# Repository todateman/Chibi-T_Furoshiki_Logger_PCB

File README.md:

# Chibi-T Furoshiki Logger

M5Stack Basic / Core2 用の車両データロガー拡張基板（モジュール基板）です。

## 概要

本基板は M5Stack の M-BUS コネクタに接続するボトムモジュールとして動作し、以下のデータを収集・記録するためのロガー回路です。

- GNSS（GPS）モジュールからの位置情報（UART）
- 車両 ECU との UART 通信によるデータ
- BME280 センサーによる温湿度・気圧などの環境データ

## 特徴

- M5Stack M-BUS（2×15ピン）接続、Basic / Core2 の両方に対応した Module 基板
  - テンプレートは <https://github.com/botanicfields/KiCad6-Environment> の `M5Stack_module_fdm` を使用
- GNSS（GPS）モジュール接続用の UART 入力
- 車両 ECU との通信用 UART 入力
- Bosch BME280 搭載（I2C接続、アドレス `0x76`）による温湿度・気圧センシング
- MP1584EN-LF-Z による +12V → 5V / 3.3V 降圧レギュレータを内蔵
- ポリヒューズおよびショットキーダイオードによる電源保護

<!-- TODO: 基板写真・回路図スクリーンショットを追加 -->

## 主要部品

| Ref | 部品 | 役割 |
| --- | --- | --- |
| U1 | MP1584EN-LF-Z | 降圧DC-DCコンバータ（+12V → 5V/3.3V） |
| U2 | BME280 | 温湿度・気圧センサー（I2C） |
| J1 | M5Stack M-BUS | M5Stack Basic/Core2 との接続コネクタ |
| D1 | ショットキーダイオード | 電源保護 |
| F1 | ポリヒューズ | 電源保護 |

より詳細な部品表は、KiCad でプロジェクトを開き BOM を出力することで確認できます（後述）。

## リポジトリ構成

```txt
Chibi-T_Furoshiki_Logger.kicad_pro   KiCadプロジェクトファイル
Chibi-T_Furoshiki_Logger.kicad_sch   回路図
Chibi-T_Furoshiki_Logger.kicad_pcb   基板データ
C15051/                              MP1584EN-LF-Z用カスタムライブラリ（シンボル・フットプリント）
logos.pretty/                        シルク印刷用ロゴフットプリント
LICENSE.txt                          ライセンス
```

## 必要な環境

- KiCad 10.0 以降

## 使い方

1. `Chibi-T_Furoshiki_Logger.kicad_pro` を KiCad 10.0 以降で開きます。
2. 回路図・基板データを確認・編集できます。
3. ガーバーデータや部品表（BOM）、部品配置データ（CPL）の生成には、KiCad拡張「[Fabrication Toolkit](https://github.com/bennymeg/Fabrication-Toolkit)」を使用する想定で設定済みです（`fabrication-toolkit-options.json`）。  
   生成したデータは `production/` フォルダに出力されますが、このフォルダは `.gitignore` 対象のためリポジトリには含まれません。  
   各自の環境で生成してください。

## 免責事項

本プロジェクトは個人のホビープロジェクトです。車両への実装・使用は自己責任で行ってください。  
基板の動作および安全性について、いかなる保証も行いません。

## ライセンス

本プロジェクトは [MIT License](LICENSE.txt) の下で公開されています。

Copyright (c) 2026 Tomohiro Kusu

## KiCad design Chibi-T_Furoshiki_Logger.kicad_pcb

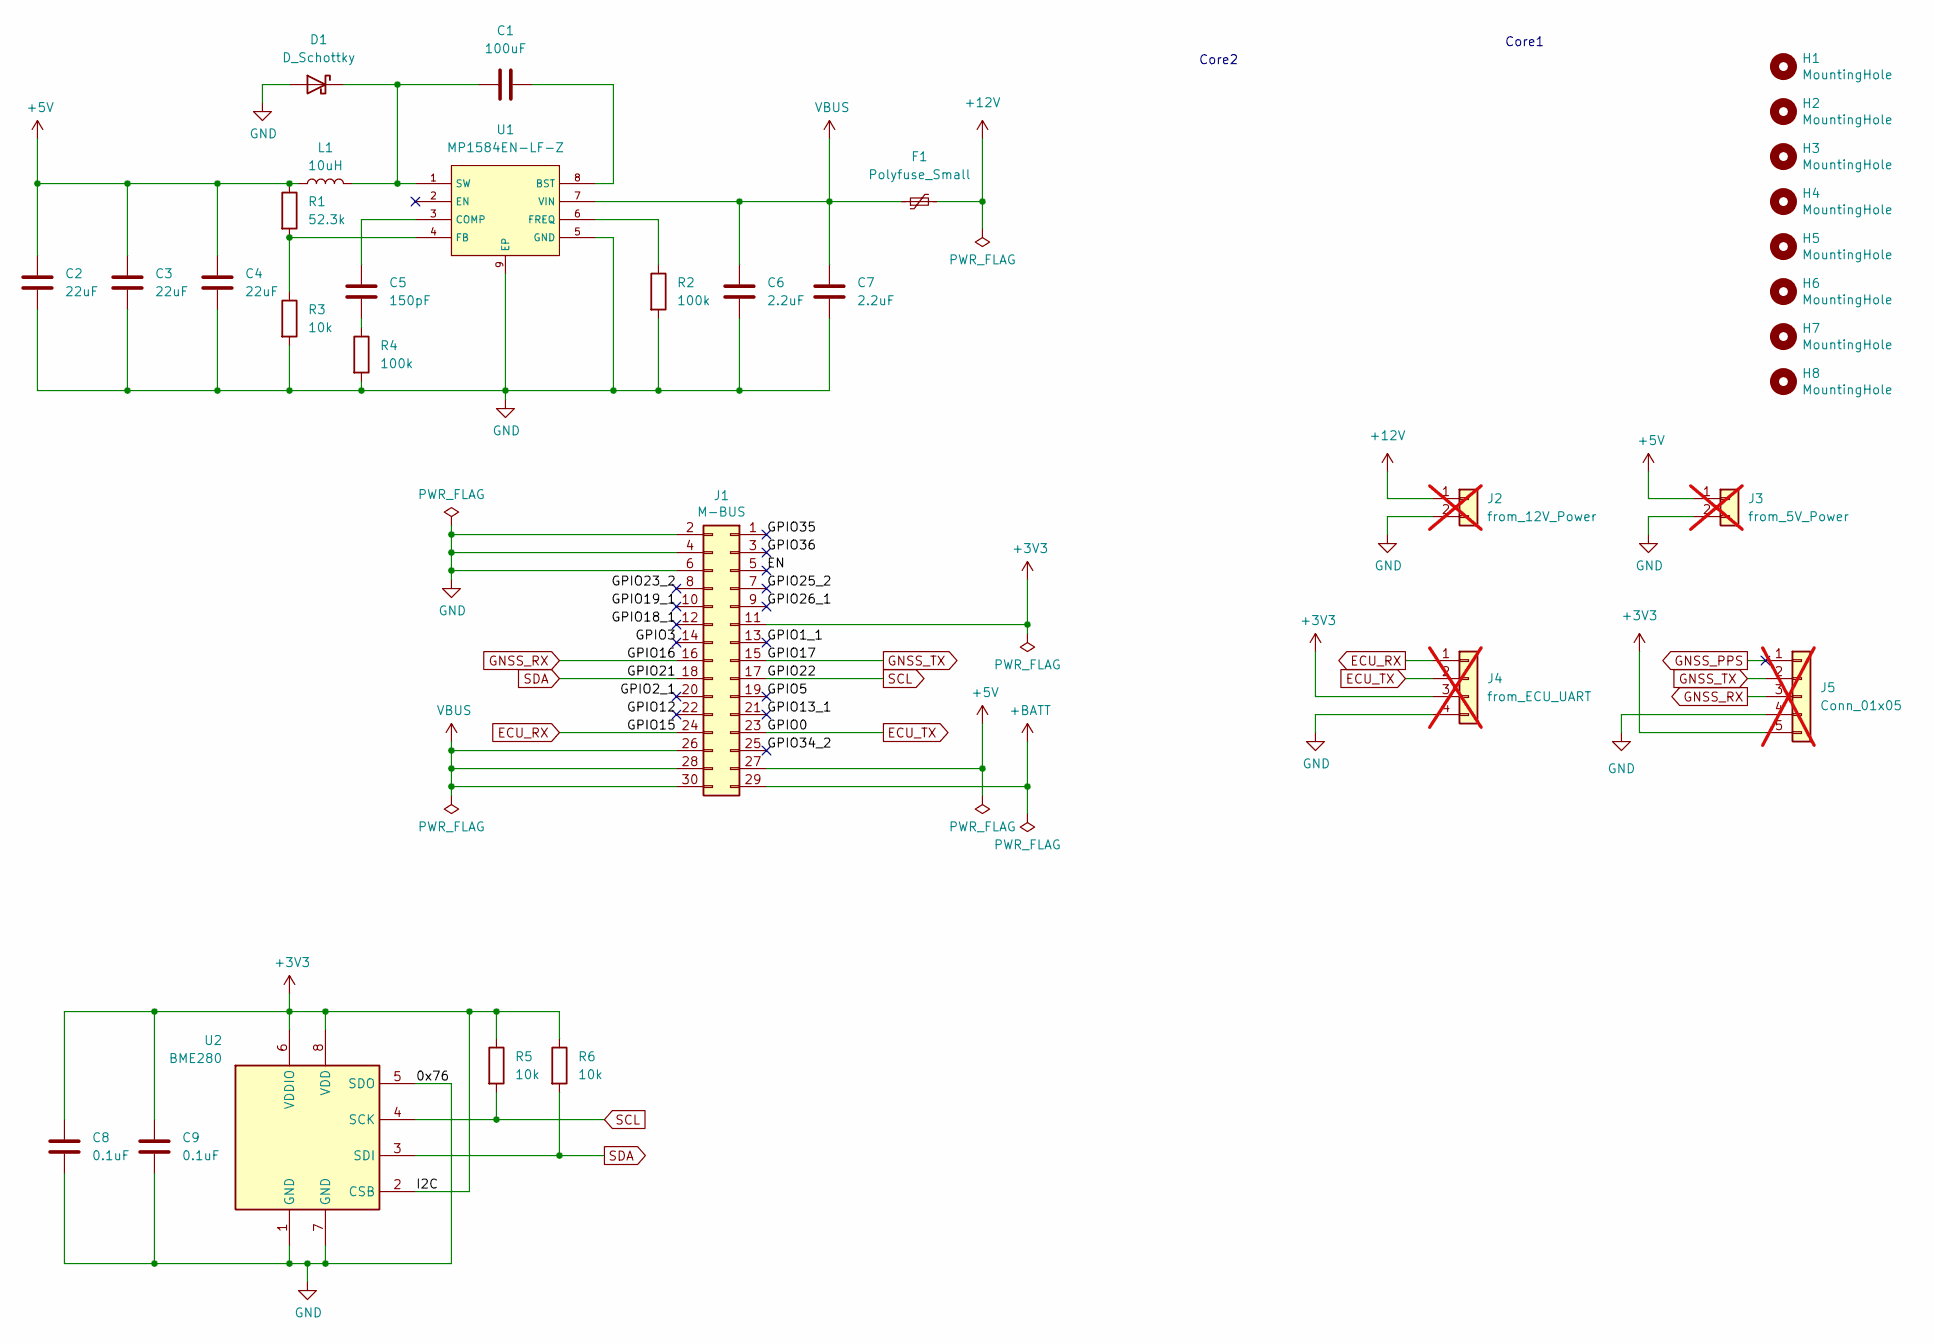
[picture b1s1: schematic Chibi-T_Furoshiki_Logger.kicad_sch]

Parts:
C1: 100uF; C_1206_3216Metric; LCSC C15008
C2, C3, C4: 22uF; C_0603_1608Metric; LCSC C59461
C5: 150pF; C_0603_1608Metric; LCSC C1594
C6, C7: 2.2uF; C_0805_2012Metric; LCSC C377773
C8, C9: 0.1uF; C_0402_1005Metric; LCSC C1525
D1: D_Schottky; D_SMA; LCSC C22452
F1: Polyfuse_Small; Fuse_1812_4532Metric; LCSC C28326708
H1, H2, H3, H4: MountingHole; BF@MountingHole_3.2mm_M3
H5, H6, H7, H8: MountingHole; BF@MountingHole_2.2mm_M2
J1: M-BUS; BF@M5Stack_MBUS
J2: from_12V_Power; PinSocket_1x02_P2.54mm_Vertical; not fitted
J3: from_5V_Power; PinSocket_1x02_P2.54mm_Vertical; not fitted
J4: from_ECU_UART; PinSocket_1x04_P2.54mm_Vertical; not fitted
J5: Conn_01x05; PinSocket_1x05_P2.54mm_Vertical; not fitted
L1: 10uH; L_Sunlord_SWPA3015S; LCSC C45403
R1: 52.3k; R_0603_1608Metric; LCSC C23198
R2, R4: 100k; R_0603_1608Metric; LCSC C25803
R3, R5, R6: 10k; R_0805_2012Metric; LCSC C17414
U1: MP1584EN-LF-Z; SOIC-8_L5.0-W4.0-P1.27-LS6.0-BL-EP2.0; Manufacturer Part MP1584EN-LF-Z; LCSC C15051
U2: BME280; Bosch_LGA-8_2.5x2.5mm_P0.65mm_ClockwisePinNumbering; LCSC C92489

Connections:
/EN: J1.5
/EN_1: J1.5
/EN_2: J1.5
/GPIO1_1: J1.13
/GPIO1_1_1: J1.13
/GPIO1_1_2: J1.13
/GPIO2_1: J1.20
/GPIO2_1_1: J1.20
/GPIO2_1_2: J1.20
/GPIO3: J1.14
/GPIO3_1: J1.14
/GPIO3_2: J1.14
/GPIO5: J1.19
/GPIO5_1: J1.19
/GPIO5_2: J1.19
/GPIO12: J1.22
/GPIO12_1: J1.22
/GPIO12_2: J1.22
/GPIO13_1: J1.21
/GPIO13_1_1: J1.21
/GPIO13_1_2: J1.21
/GPIO18_1: J1.12
/GPIO18_1_1: J1.12
/GPIO18_1_2: J1.12
/GPIO19_1: J1.10
/GPIO19_1_1: J1.10
/GPIO19_1_2: J1.10
/GPIO23_2: J1.8
/GPIO23_2_1: J1.8
/GPIO23_2_2: J1.8
/GPIO25_2: J1.7
/GPIO25_2_1: J1.7
/GPIO25_2_2: J1.7
/GPIO26_1: J1.9
/GPIO26_1_1: J1.9
/GPIO26_1_2: J1.9
/GPIO34_2: J1.25
/GPIO34_2_1: J1.25
/GPIO34_2_2: J1.25
/GPIO35: J1.1
/GPIO35_1: J1.1
/GPIO35_2: J1.1
/GPIO36: J1.3
/GPIO36_1: J1.3
/GPIO36_2: J1.3
ECU_RX: J1.24, J4.1
ECU_TX: J1.23, J4.2
GNSS_PPS: J5.1
GNSS_RX: J1.16, J5.3
GNSS_TX: J1.15, J5.2
unnamed: C5.1, R4.1
unnamed: C1.1, D1.1 (K), L1.2, U1.1 (SW)
unnamed: C1.2, U1.8 (BST)
unnamed: C5.2, U1.3 (COMP)
unnamed: R1.2, R3.1, U1.4 (FB)
unnamed: R2.1, U1.6 (FREQ)
SCL: J1.17, R5.2, U2.4 (SCK)
SDA: J1.18, R6.2, U2.3 (SDI)

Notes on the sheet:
Core1
Core2

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
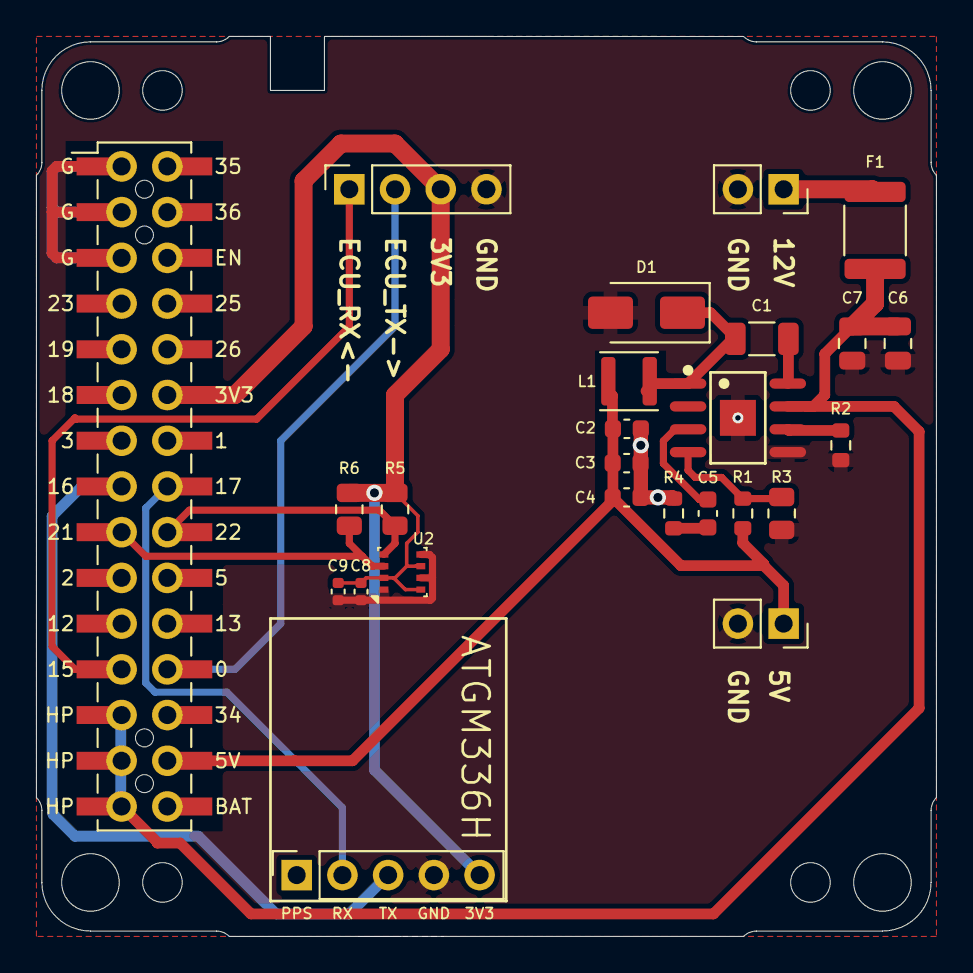
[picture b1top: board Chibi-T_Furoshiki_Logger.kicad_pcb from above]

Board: 2 copper layers, 50.0 x 50.0 mm, 33 parts (0 on the bottom side), 17 nets.

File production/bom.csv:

Designator,Footprint,Quantity,Value,LCSC Part #
C1,1206,1,100uF,C15008
"C2, C3, C4",0603,3,22uF,C59461
C5,0603,1,150pF,C1594
"C6, C7",0805,2,2.2uF,C377773
"C8, C9",0402,2,0.1uF,C1525
D1,D_SMA,1,D_Schottky,C22452
F1,1812,1,Polyfuse_Small,C28326708
"H1, H2, H3, H4",BF@MountingHole_3.2mm_M3,4,MountingHole,
"H5, H6, H7, H8",BF@MountingHole_2.2mm_M2,4,MountingHole,
J1,BF@M5Stack_MBUS,1,M-BUS,
L1,L_Sunlord_SWPA3015S,1,10uH,C45403
R1,0603,1,52.3k,C23198
"R2, R4",0603,2,100k,C25803
"R3, R5, R6",0805,3,10k,C17414
U1,SOIC-8_L5.0-W4.0-P1.27-LS6.0-BL-EP2.0,1,MP1584EN-LF-Z,C15051
U2,Bosch_LGA-8_2.5x2.5mm_P0.65mm_ClockwisePinNumbering,1,BME280,C92489
